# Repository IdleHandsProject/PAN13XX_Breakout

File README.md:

PAN13XX_Breakout
================

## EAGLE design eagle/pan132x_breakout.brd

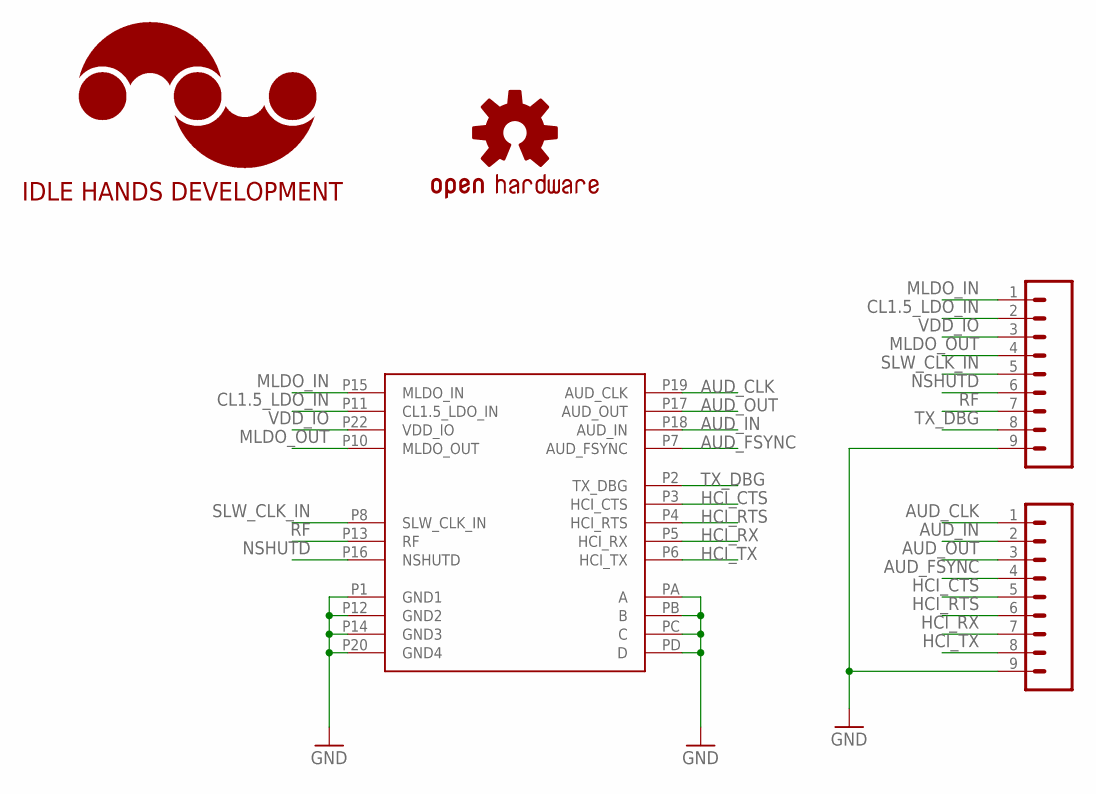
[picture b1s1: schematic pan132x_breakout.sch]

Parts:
JP1, JP2: M09LOCK; 1X09_LOCK
LOGO1: IDLEHANDS_LOGOL; IHD-LOGO-L
LOGO2: OSHW-LOGOS; OSHW-LOGO-S
U$1: PAN132X; PAN13XX

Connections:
AUD_CLK: JP2.1, U$1.P19 (AUD_CLK)
AUD_FSYNC: JP2.4, U$1.P7 (AUD_FSYNC)
AUD_IN: JP2.2, U$1.P18 (AUD_IN)
AUD_OUT: JP2.3, U$1.P17 (AUD_OUT)
CL1.5_LDO_IN: JP1.2, U$1.P11 (CL1.5_LDO_IN)
GND: JP1.9, JP2.9, U$1.P1 (GND1), U$1.P12 (GND2), U$1.P14 (GND3), U$1.P20 (GND4), U$1.PA (A), U$1.PB (B), U$1.PC (C), U$1.PD (D)
HCI_CTS: JP2.5, U$1.P3 (HCI_CTS)
HCI_RTS: JP2.6, U$1.P4 (HCI_RTS)
HCI_RX: JP2.7, U$1.P5 (HCI_RX)
HCI_TX: JP2.8, U$1.P6 (HCI_TX)
MLDO_IN: JP1.1, U$1.P15 (MLDO_IN)
MLDO_OUT: JP1.4, U$1.P10 (MLDO_OUT)
NSHUTD: JP1.6, U$1.P16 (NSHUTD)
RF: JP1.7, U$1.P13 (RF)
SLW_CLK_IN: JP1.5, U$1.P8 (SLW_CLK_IN)
TX_DBG: JP1.8, U$1.P2 (TX_DBG)
VDD_IO: JP1.3, U$1.P22 (VDD_IO)

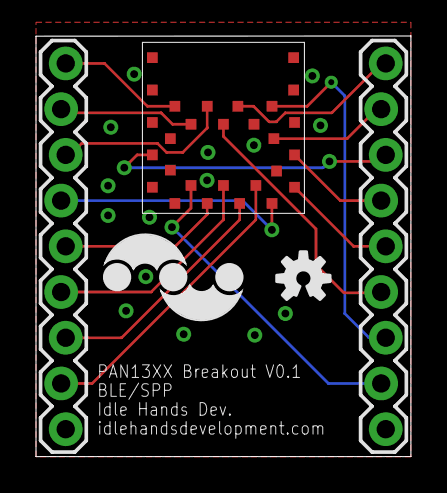
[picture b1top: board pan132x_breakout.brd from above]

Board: 2 copper layers, 20.8 x 23.4 mm, 5 parts (0 on the bottom side), 17 nets.

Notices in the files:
parts and their libraries:
SparkFun-Connectors: Licensing: CC v3.0 Share-Alike You are welcome to use this library for commercial purposes.
